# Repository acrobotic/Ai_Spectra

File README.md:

## Ai\_Spectra

PCB design files (EAGLE) for an interactive Light+Sound Electronics Board 
carrying 48 RGB LEDs, sensors, and a speaker for displaying custom audiovisual
patterns. 

## Description

For more details, check out the product page at:

   * https://acrobotic.com/acr-00018

Designed by ACROBOTIC Industries.  Please consider buying products from us to 
help fund future Open-Source projects like this! We’ll always put our best 
effort in every project, and release all our design files and code for you to 
use. 

## License

Released under the Creative Commons Attribution, Share-Alike license. Please 
check LICENSE.txt for more information. All text above must be included in any 
redistribution.

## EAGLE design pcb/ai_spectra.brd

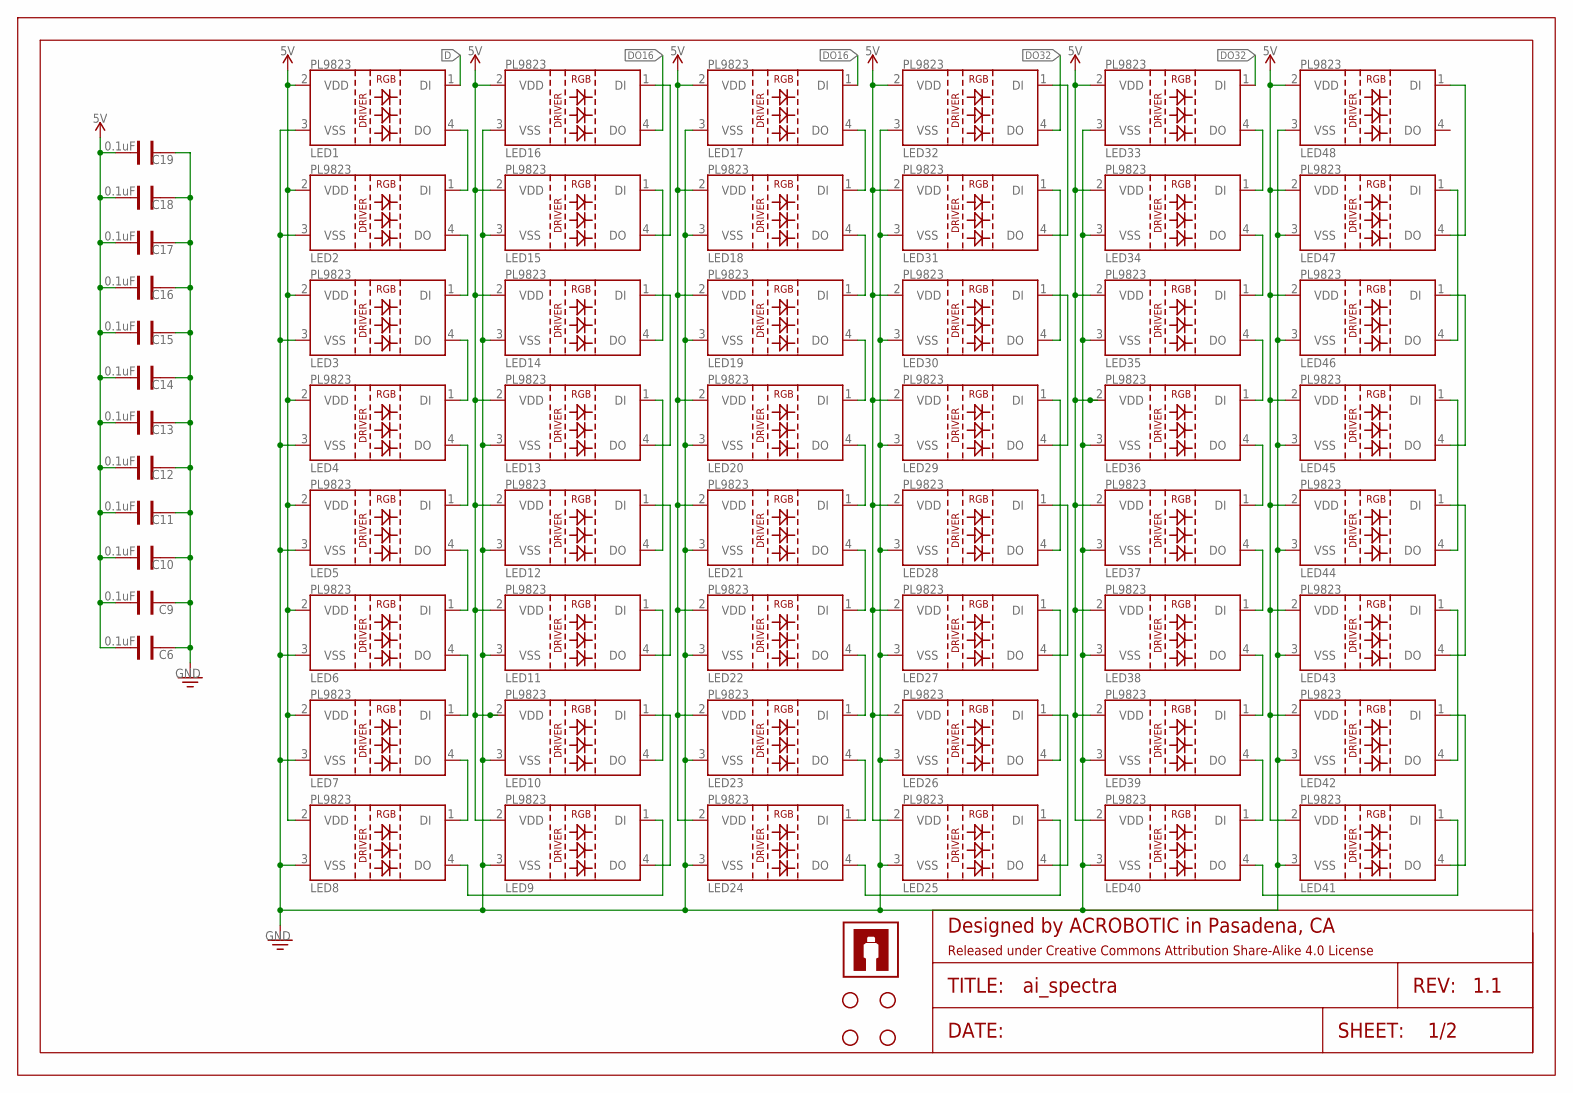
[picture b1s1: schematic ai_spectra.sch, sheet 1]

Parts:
C6, C9, C10, C11, C12, C13, C14, C15, C16, C17, C18, C19: 0.1uF; CAP-025X050
FRAME1: FRAME-LETTER; CREATIVE-COMMONS
LED1, LED2, LED3, LED4, LED5, LED6, LED7, LED8, LED9, LED10, LED11, LED12, LED13, LED14, LED15, LED16, LED17, LED18, LED19, LED20, LED21, LED22, LED23, LED24, LED25, LED26, LED27, LED28, LED29, LED30, LED31, LED32, LED33, LED34, LED35, LED36, LED37, LED38, LED39, LED40, LED41, LED42, LED43, LED44, LED45, LED46, LED47, LED48: LED-PL9823-F8
STANDOFF1, STANDOFF2, STANDOFF3, STANDOFF4: STAND-OFF4; STAND-OFF-4
U$18: AI-LOGOXS; AI-LOGO-XS

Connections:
5V: C6.1, C9.1, C10.1, C11.1, C12.1, C13.1, C14.1, C15.1, C16.1, C17.1, C18.1, C19.1, LED1.2 (VDD), LED2.2 (VDD), LED3.2 (VDD), LED4.2 (VDD), LED5.2 (VDD), LED6.2 (VDD), LED7.2 (VDD), LED8.2 (VDD), LED9.2 (VDD), LED10.2 (VDD), LED11.2 (VDD), LED12.2 (VDD), LED13.2 (VDD), LED14.2 (VDD), LED15.2 (VDD), LED16.2 (VDD), LED17.2 (VDD), LED18.2 (VDD), LED19.2 (VDD), LED20.2 (VDD), LED21.2 (VDD), LED22.2 (VDD), LED23.2 (VDD), LED24.2 (VDD), LED25.2 (VDD), LED26.2 (VDD), LED27.2 (VDD), LED28.2 (VDD), LED29.2 (VDD), LED30.2 (VDD), LED31.2 (VDD), LED32.2 (VDD), LED33.2 (VDD), LED34.2 (VDD), LED35.2 (VDD), LED36.2 (VDD), LED37.2 (VDD), LED38.2 (VDD), LED39.2 (VDD), LED40.2 (VDD), LED41.2 (VDD), LED42.2 (VDD), LED43.2 (VDD), LED44.2 (VDD), LED45.2 (VDD), LED46.2 (VDD), LED47.2 (VDD), LED48.2 (VDD); also elsewhere on the board
D: LED1.1 (DI); also elsewhere on the board
DO8: LED8.4 (DO), LED9.1 (DI)
DO16: LED16.4 (DO), LED17.1 (DI)
DO24: LED24.4 (DO), LED25.1 (DI)
DO32: LED32.4 (DO), LED33.1 (DI)
GND: C6.2, C9.2, C10.2, C11.2, C12.2, C13.2, C14.2, C15.2, C16.2, C17.2, C18.2, C19.2, LED1.3 (VSS), LED2.3 (VSS), LED3.3 (VSS), LED4.3 (VSS), LED5.3 (VSS), LED6.3 (VSS), LED7.3 (VSS), LED8.3 (VSS), LED9.3 (VSS), LED10.3 (VSS), LED11.3 (VSS), LED12.3 (VSS), LED13.3 (VSS), LED14.3 (VSS), LED15.3 (VSS), LED16.3 (VSS), LED17.3 (VSS), LED18.3 (VSS), LED19.3 (VSS), LED20.3 (VSS), LED21.3 (VSS), LED22.3 (VSS), LED23.3 (VSS), LED24.3 (VSS), LED25.3 (VSS), LED26.3 (VSS), LED27.3 (VSS), LED28.3 (VSS), LED29.3 (VSS), LED30.3 (VSS), LED31.3 (VSS), LED32.3 (VSS), LED33.3 (VSS), LED34.3 (VSS), LED35.3 (VSS), LED36.3 (VSS), LED37.3 (VSS), LED38.3 (VSS), LED39.3 (VSS), LED40.3 (VSS), LED41.3 (VSS), LED42.3 (VSS), LED43.3 (VSS), LED44.3 (VSS), LED45.3 (VSS), LED46.3 (VSS), LED47.3 (VSS), LED48.3 (VSS); also elsewhere on the board
unnamed: LED1.4 (DO), LED2.1 (DI)
unnamed: LED2.4 (DO), LED3.1 (DI)
unnamed: LED3.4 (DO), LED4.1 (DI)
unnamed: LED4.4 (DO), LED5.1 (DI)
unnamed: LED5.4 (DO), LED6.1 (DI)
unnamed: LED6.4 (DO), LED7.1 (DI)
unnamed: LED7.4 (DO), LED8.1 (DI)
unnamed: LED9.4 (DO), LED10.1 (DI)
unnamed: LED10.4 (DO), LED11.1 (DI)
unnamed: LED11.4 (DO), LED12.1 (DI)
unnamed: LED12.4 (DO), LED13.1 (DI)
unnamed: LED13.4 (DO), LED14.1 (DI)
unnamed: LED14.4 (DO), LED15.1 (DI)
unnamed: LED15.4 (DO), LED16.1 (DI)
unnamed: LED33.4 (DO), LED34.1 (DI)
unnamed: LED17.4 (DO), LED18.1 (DI)
unnamed: LED18.4 (DO), LED19.1 (DI)
unnamed: LED19.4 (DO), LED20.1 (DI)
unnamed: LED20.4 (DO), LED21.1 (DI)
unnamed: LED21.4 (DO), LED22.1 (DI)
unnamed: LED22.4 (DO), LED23.1 (DI)
unnamed: LED23.4 (DO), LED24.1 (DI)
unnamed: LED34.4 (DO), LED35.1 (DI)
unnamed: LED35.4 (DO), LED36.1 (DI)
unnamed: LED36.4 (DO), LED37.1 (DI)
unnamed: LED37.4 (DO), LED38.1 (DI)
unnamed: LED38.4 (DO), LED39.1 (DI)
unnamed: LED39.4 (DO), LED40.1 (DI)
unnamed: LED40.4 (DO), LED41.1 (DI)
unnamed: LED25.4 (DO), LED26.1 (DI)
unnamed: LED26.4 (DO), LED27.1 (DI)
unnamed: LED27.4 (DO), LED28.1 (DI)
unnamed: LED28.4 (DO), LED29.1 (DI)
unnamed: LED29.4 (DO), LED30.1 (DI)
unnamed: LED30.4 (DO), LED31.1 (DI)
unnamed: LED31.4 (DO), LED32.1 (DI)
unnamed: LED41.4 (DO), LED42.1 (DI)
unnamed: LED42.4 (DO), LED43.1 (DI)
unnamed: LED43.4 (DO), LED44.1 (DI)
unnamed: LED44.4 (DO), LED45.1 (DI)
unnamed: LED45.4 (DO), LED46.1 (DI)
unnamed: LED46.4 (DO), LED47.1 (DI)
unnamed: LED47.4 (DO), LED48.1 (DI)

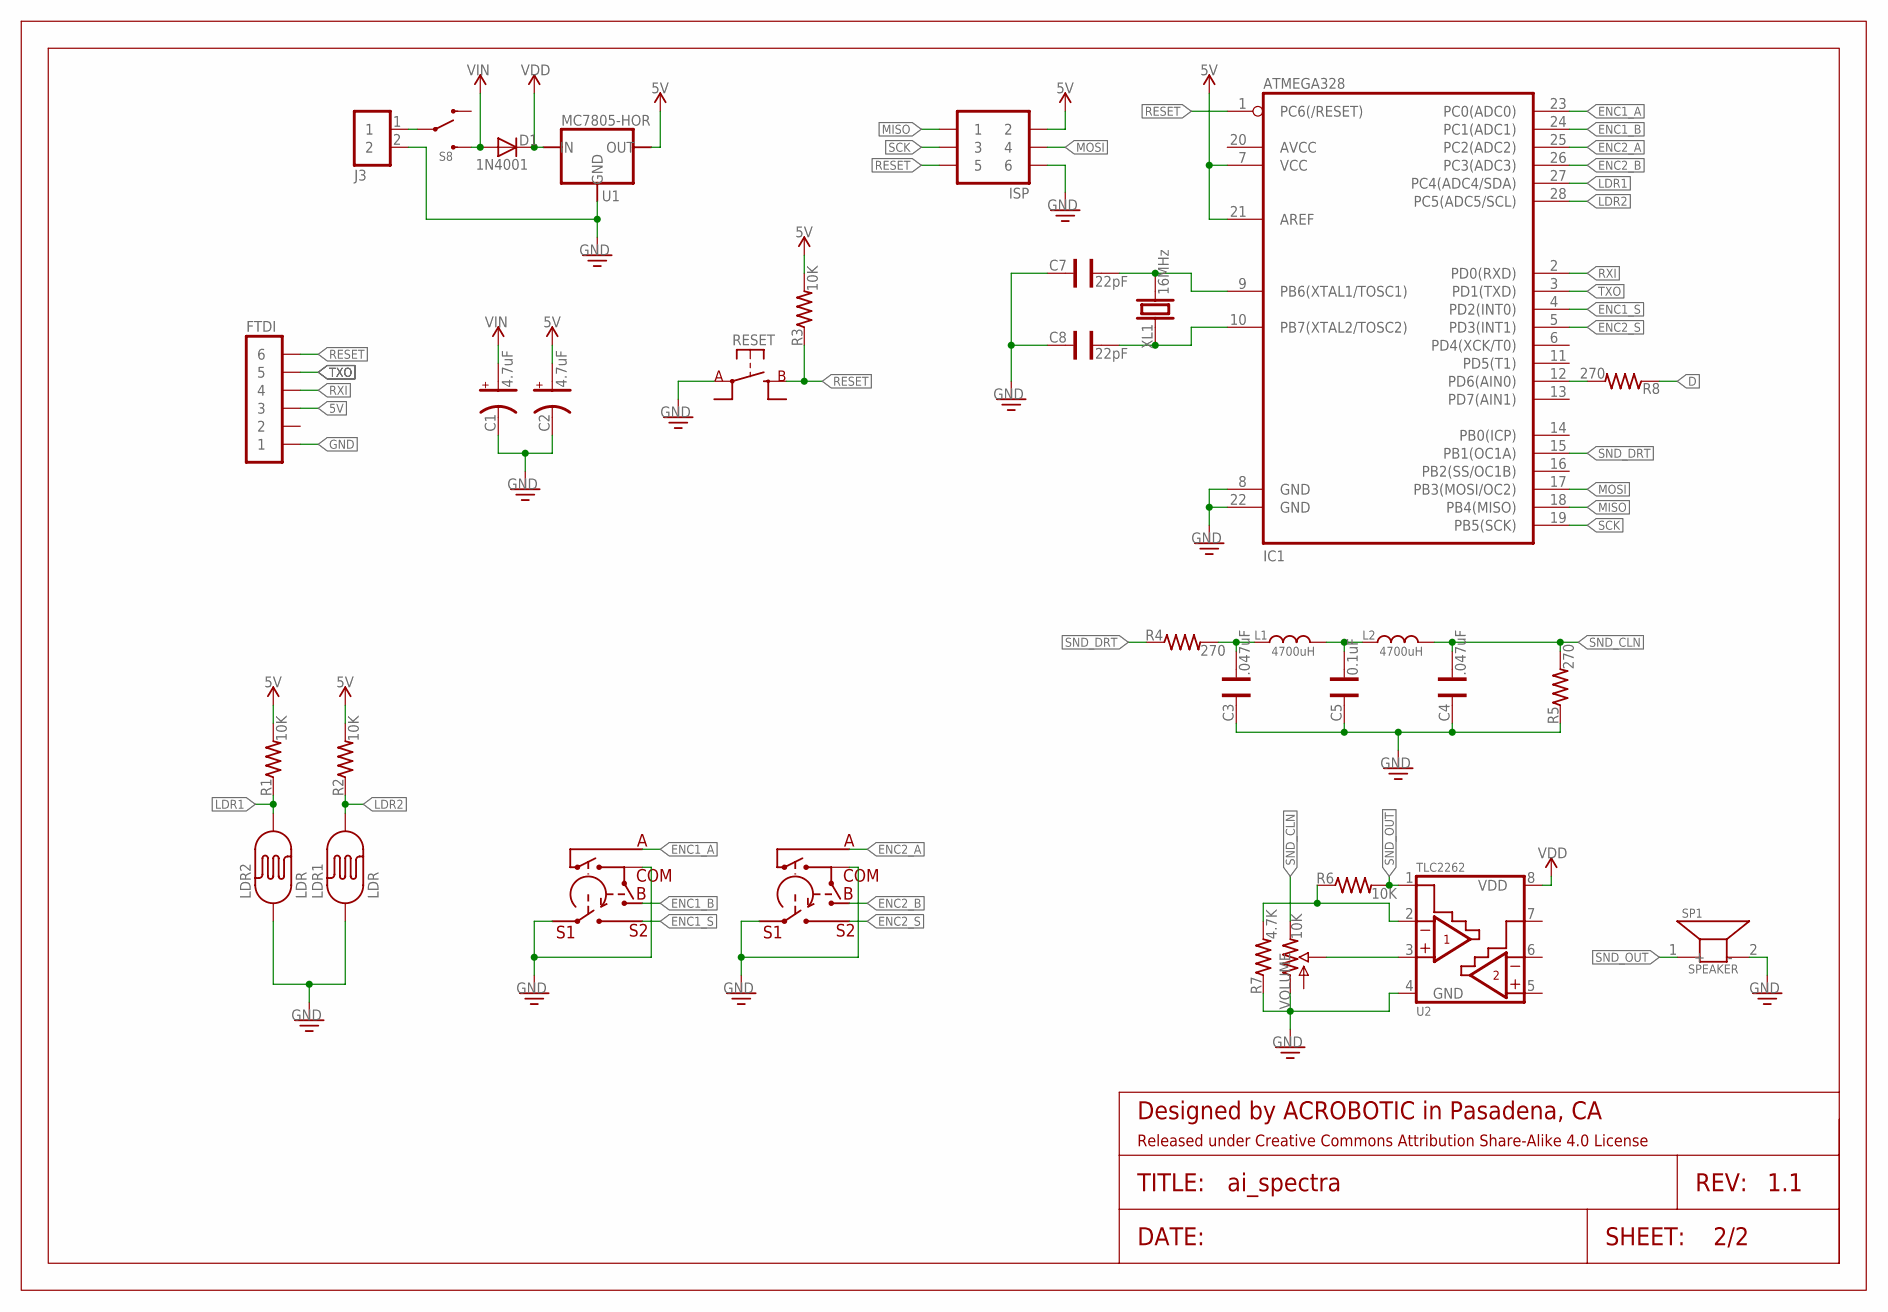
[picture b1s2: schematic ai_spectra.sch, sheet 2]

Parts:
C1, C2: 4.7uF; CAP-POL-025X50
C3, C4: .047uF; CAP-025X050
C5: 0.1uF; CAP-025X050
C7, C8: 22pF; CAP-025X050
D1: 1N4001; TH-1N914
ENC1, ENC2: ROT-ENC; ROTENC-12MM-SW
FRAME2: FRAME-LETTER; CREATIVE-COMMONS
FTDI: 1X06
IC1: ATMEGA328P-PDIP; DIL28
ISP: 2X03
J3: 1X02ST; 1X02-ST
L1, L2: 4700uH; RLB0912
LDR1, LDR2: LDR-PTH; LDR
R1, R2, R3, R6: 10K; RES-AXIAL-0.4
R4, R5, R8: 270; RES-AXIAL-0.4
R7: 4.7K; RES-AXIAL-0.4
RESET: SW-SPSTTH06X06; SW-SPST-TH06X06
S8: SW-SPDTTH; SW-SPDT-TH
SP1: SPEAKER; AL30P
U1: MC7805-HOR; TO220
U2: TLC2262; DIL08
VOLUME: 10K; POT-05X05
XL1: 16MHz; HC49S

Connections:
5V: C2.A, FTDI.3, IC1.7 (VCC), IC1.21 (AREF), ISP.2, R1.P$2 (2), R2.P$2 (2), R3.P$2 (2), U1.OUT; also elsewhere on the board
D: R8.P$1 (1); also elsewhere on the board
ENC1_A: ENC1.P3 (A), IC1.23 (PC0(ADC0))
ENC1_B: ENC1.P1 (B), IC1.24 (PC1(ADC1))
ENC1_S: ENC1.P5 (S2), IC1.4 (PD2(INT0))
ENC2_A: ENC2.P3 (A), IC1.25 (PC2(ADC2))
ENC2_B: ENC2.P1 (B), IC1.26 (PC3(ADC3))
ENC2_S: ENC2.P5 (S2), IC1.5 (PD3(INT1))
GND: C1.C, C2.C, C3.2, C4.2, C5.2, C7.2, C8.2, ENC1.P2 (COM), ENC1.P4 (S1), ENC2.P2 (COM), ENC2.P4 (S1), FTDI.1, IC1.8 (GND), IC1.22 (GND), ISP.6, J3.2, LDR1.1, LDR2.1, R5.P$1 (1), R7.P$1 (1), RESET.A@1 (A), SP1.2 (-), U1.GND, U2.4 (GND), VOLUME.3 (A); also elsewhere on the board
LDR1: IC1.27 (PC4(ADC4/SDA)), LDR2.2, R1.P$1 (1)
LDR2: IC1.28 (PC5(ADC5/SCL)), LDR1.2, R2.P$1 (1)
MISO: IC1.18 (PB4(MISO)), ISP.1
MOSI: IC1.17 (PB3(MOSI/OC2)), ISP.4
unnamed: U2.3 (1IN+), VOLUME.2 (S)
unnamed: C8.1, IC1.10 (PB7(XTAL2/TOSC2)), XL1.1
unnamed: C7.1, IC1.9 (PB6(XTAL1/TOSC1)), XL1.2
unnamed: J3.1, S8.2 (COM)
unnamed: C3.1, L1.2, R4.P$2 (2)
unnamed: C5.1, L1.1, L2.2
unnamed: R6.P$1 (1), R7.P$2 (2), U2.2 (1IN-)
unnamed: IC1.12 (PD6(AIN0)), R8.P$2 (2)
RESET: FTDI.6, IC1.1 (PC6(/RESET)), ISP.5, R3.P$1 (1), RESET.B@1 (B)
RXI: FTDI.4, IC1.2 (PD0(RXD))
SCK: IC1.19 (PB5(SCK)), ISP.3
SND_CLN: C4.1, L2.1, R5.P$2 (2), VOLUME.1 (E)
SND_DRT: IC1.15 (PB1(OC1A)), R4.P$1 (1)
SND_OUT: R6.P$2 (2), SP1.1 (+), U2.1 (1OUT)
TXO: FTDI.5, IC1.3 (PD1(TXD))
VDD: D1.C, U1.IN, U2.8 (VDD)
VIN: C1.A, D1.A, S8.3 (L2)

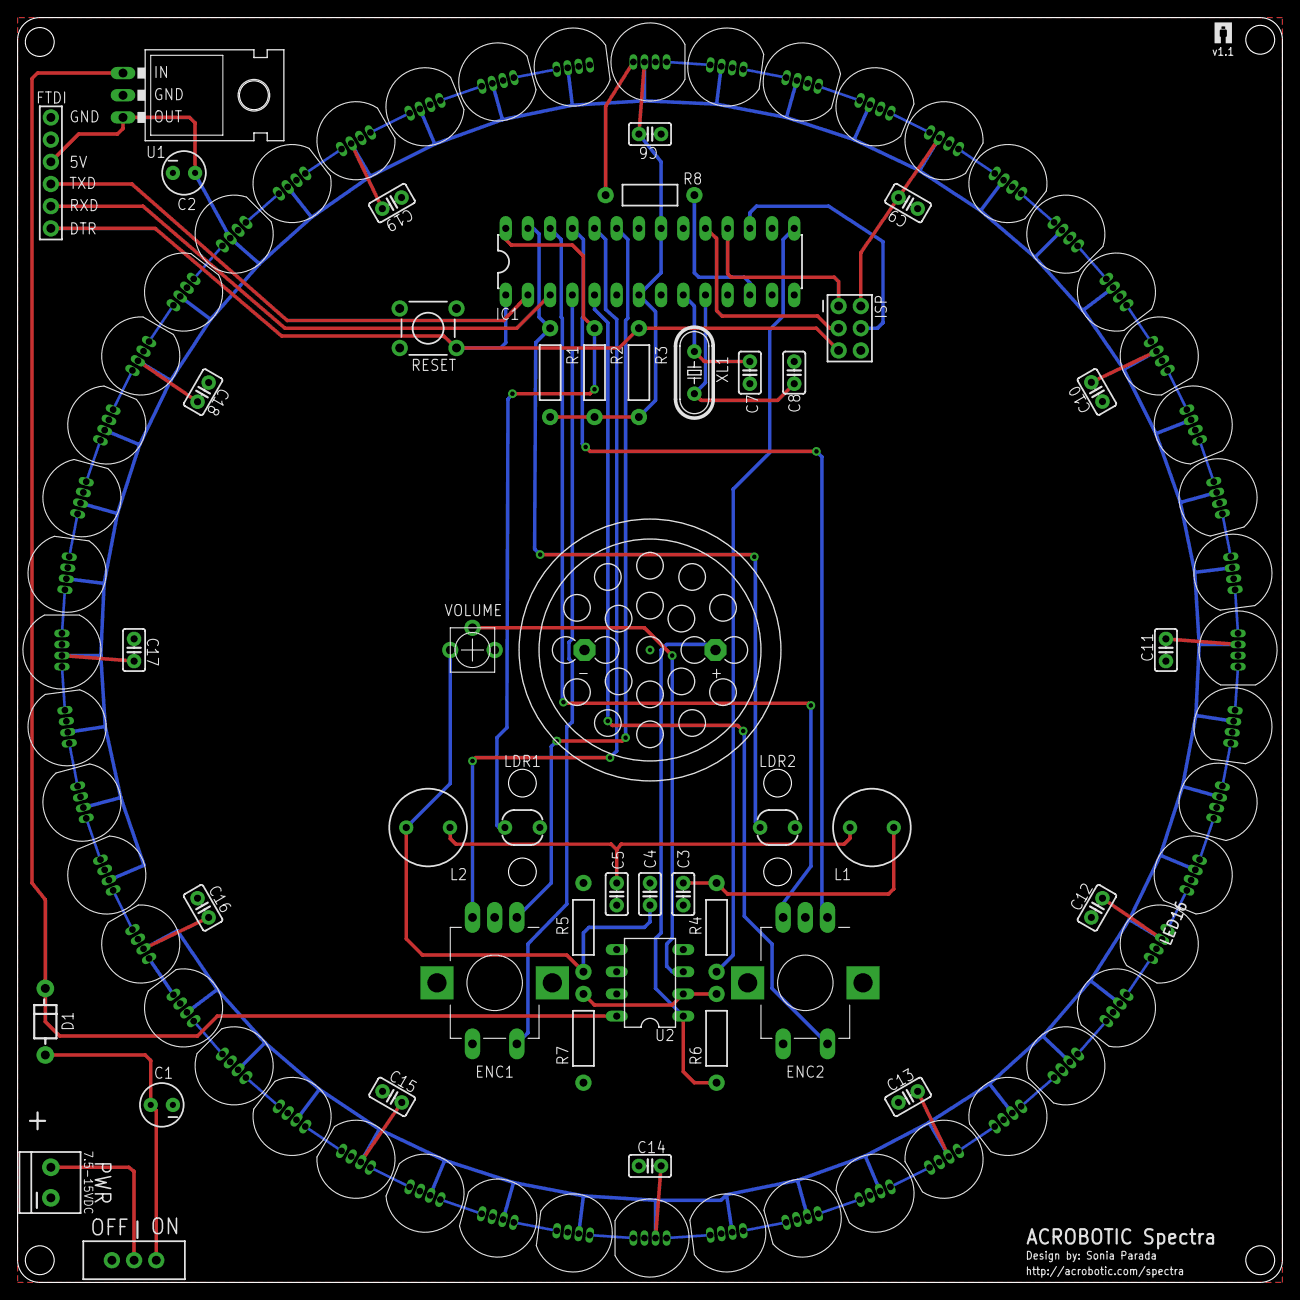
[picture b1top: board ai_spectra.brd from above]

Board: 2 copper layers, 144.8 x 144.8 mm, 100 parts (0 on the bottom side), 77 nets.

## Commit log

2015-09-26 first commit.
2015-09-28 adding gerbers
2015-09-29 updating license, and schematic
2015-11-08 updating LED spacing
2015-11-08 updating attribute

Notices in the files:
parts and their libraries:
Ai_Miscellany: Attribution Share-Alike 4.0 License
Ai_Miscellany: https://creativecommons.org/licenses/by-sa/4.0
Ai_Miscellany: Released under Creative Commons Attribution Share-Alike 4.0 License
